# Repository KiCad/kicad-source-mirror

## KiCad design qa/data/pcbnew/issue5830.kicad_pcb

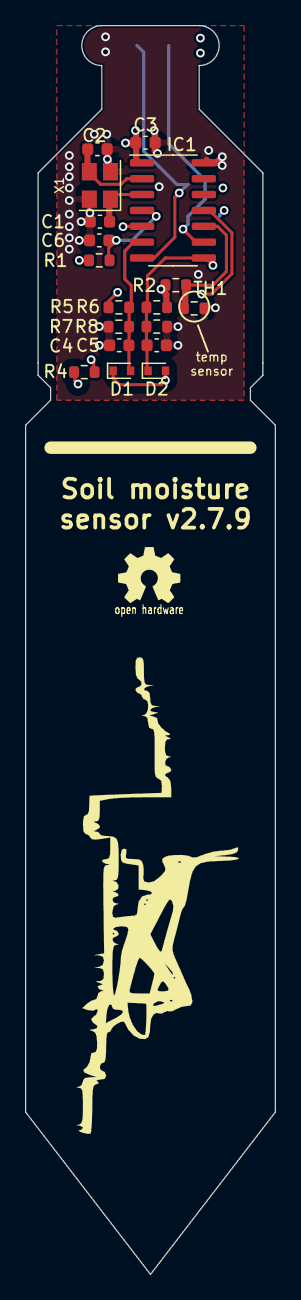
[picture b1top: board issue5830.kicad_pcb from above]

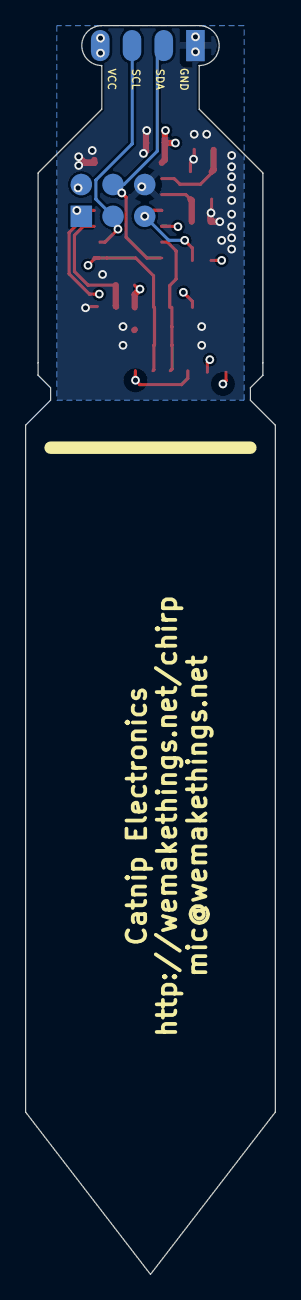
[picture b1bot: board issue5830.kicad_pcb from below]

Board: 4 copper layers, 20.0 x 100.0 mm, 20 parts (2 on the bottom side), 13 nets.

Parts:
C1: 33p; C_0603_1608Metric
C2: 33pp; C_0603_1608Metric
C3, C6: 1u; C_0603_1608Metric
C4, C5: 1n; C_0603_1608Metric
D1, D2: BAT54; D_SOD-523
IC1: ATTINY441-SSU; SOIC-14_3.9x8.7mm_P1.27mm
P1: CONN_02X03; Pin_Header_Straight_2x03
P2: CONN_01X04; Pin_Header_Straight_1x04_Pitch2.54mm
R1: 10k; R_0603_1608Metric
R2: 10k 0.1%; R_0603_1608Metric
R4: 330; R_0603_1608Metric
R5, R6, R7, R8: 1M; R_0603_1608Metric
TH1: NCP18XH103F03RB; R_0603_1608Metric
X1: 16MHz; Crystal_SMD_3225-4pin_3.2x2.5mm

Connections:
/EXCITATION: IC1.5, R4.2
/MISO/SENSE_HIGH: C5.1, D2.2, IC1.8, P1.1, R6.1, R8.2
/MOSI/SDA: IC1.7, P1.4, P2.2
/RESET: C6.1, IC1.4, P1.5, R1.1
/SCK/SCL: IC1.9, P1.3, P2.3
/SENSE_LOW: C4.1, D1.1, IC1.6, R5.1, R7.2
/SENSOR_TRACK: D1.2, D2.1, R4.1
/THERMISTOR: IC1.10, R2.2, TH1.1
GND: C1.2, C2.2, C3.2, C4.2, C5.2, C6.2, IC1.14, P1.6, P2.1, R7.1, R8.1, TH1.2, X1.2, X1.4
unnamed: C1.1, IC1.3, X1.1
unnamed: C2.1, IC1.2, X1.3
unnamed: IC1.11, R2.1, R5.2, R6.2
VCC: C3.1, IC1.1, P1.2, P2.4, R1.2

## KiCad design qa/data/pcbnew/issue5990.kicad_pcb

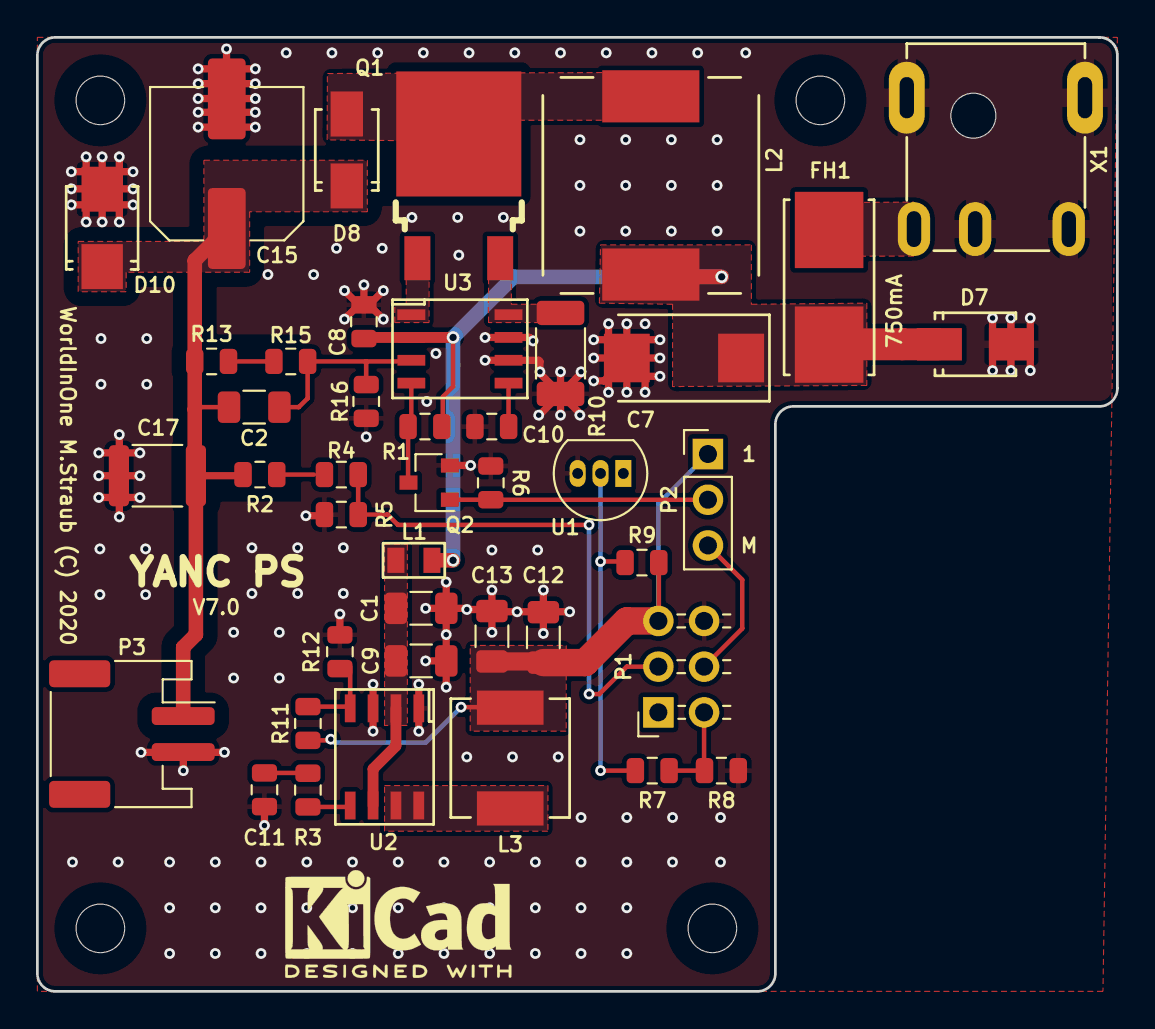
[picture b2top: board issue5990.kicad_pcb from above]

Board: 2 copper layers, 60.0 x 53.0 mm, 46 parts (0 on the bottom side), 23 nets.

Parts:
C1, C9, C12, C13: 22µ; C_1206_3216Metric_95
C2: 100P; C_1206_3216Metric_95
C7: 100µ; Tantalum_Case-D_EIA-7343-31_Reflow
C8, C10: 100N; C_0805_2012Metric_60
C11: 2.7N; C_0805_2012Metric_60
C15: 3.3µ; C_Elec_8x10.2
C17: 100N; C_1812_4532Metric
D7: SS34; SMA_Standard
D8: ES1G; SMA_Standard
D10: SMBJ5388B; SMB_Standard
FH1: FH1808; Littelfuse_Nano2_1808_Fuse_Holder_SMD
L1: FB0805; INDC2012X110
L2: 100µ; CDRH127
L3: 10µ; Inductor_0630
MH1, MH2, MH3, MH4: Mounting_Hole; MountingHole_2.7mm_M2.5_DIN965
P1: FE03-2W; PinSocket_2x03_P2.54mm_Horizontal
P2: MA03-1; PinHeader_1x03_P2.54mm_Vertical
P3: JSTPHMHS-2; JST_PH_S2B-PH-SM4-TB_1x02-1MP_P2.00mm_Horizontal
Q1: FQD18N20; TO-252
Q2: BSS138; SOT-23
R1, R3: 22K; R_0805_2012Metric
R2, R13, R15: 470K; R_0805_2012Metric
R4, R6, R8, R12: 10K; R_0805_2012Metric
R5: 3.9K; R_0805_2012Metric
R7: 15K; R_0805_2012Metric
R9: 1K; R_0805_2012Metric
R10: 0.05E; R_2010_5025Metric
R11: 52.3K; R_0805_2012Metric
R16: 8.2K; R_0805_2012Metric
U1: LM335Z; TO-92_Inline_Narrow_Oval
U2: AOZ1015AI; SOIC-8_3.9x4.9mm_Pitch1.27mm
U3: MAX1771; SOIC-8_3.9x4.9mm_Pitch1.27mm
X1: PJ-051A

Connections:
/5V: C12.2, C13.2, L3.2, P1.5, P2.1, R9.1, R11.2
/170V: C2.1, C15.1, C17.1, D8.1 (K), D10.1 (K), P3.1, R2.2, R13.2
/CASETEMP: P1.2, R7.2, R8.1
/HVON: P1.4, P2.3
/U170V: P1.3, R4.1, R5.2
/UB: C1.2, C9.2, L1.2, U2.2 (VIN), U2.6 (EN)
/UIN: C7.1, C8.1, D7.1 (K), FH1.2, L1.1, L2.1, R1.2, U3.2 (VCC)
GND: C1.1, C7.2, C8.2, C9.1, C10.2, C11.1, C12.1, C13.1, C15.2, C17.2, D7.2 (A), D10.2 (A), P1.6, P3.2, Q2.2 (S), R5.1, R6.1, R8.2, R10.2, R12.1, R16.1, U1.3 (-), U2.1 (PGND), U2.3 (AGND), U3.6 (AGND), U3.7 (GND), X1.2, X1.3, X1.CASE (CASE1)
unnamed: C2.2, R15.1, R16.2, U3.3 (FB)
unnamed: C10.1, U3.5 (REF)
unnamed: C11.2, R3.1
unnamed: D8.2 (A), L2.2, Q1.3 (D)
unnamed: FH1.1, X1.1
unnamed: L3.1, U2.7 (LX), U2.8 (LX)
unnamed: P2.2, Q2.1 (G), R6.2
unnamed: Q1.1 (G), U3.1 (EXT)
unnamed: Q1.2 (S), R10.1, U3.8 (CS)
unnamed: Q2.3 (D), R1.1, U3.4 (SHDN)
unnamed: R2.1, R4.2
unnamed: R3.2, U2.5 (COMP)
unnamed: R7.1, R9.2, U1.2 (+)
unnamed: R11.1, R12.2, U2.4 (FB)
unnamed: R13.1, R15.2

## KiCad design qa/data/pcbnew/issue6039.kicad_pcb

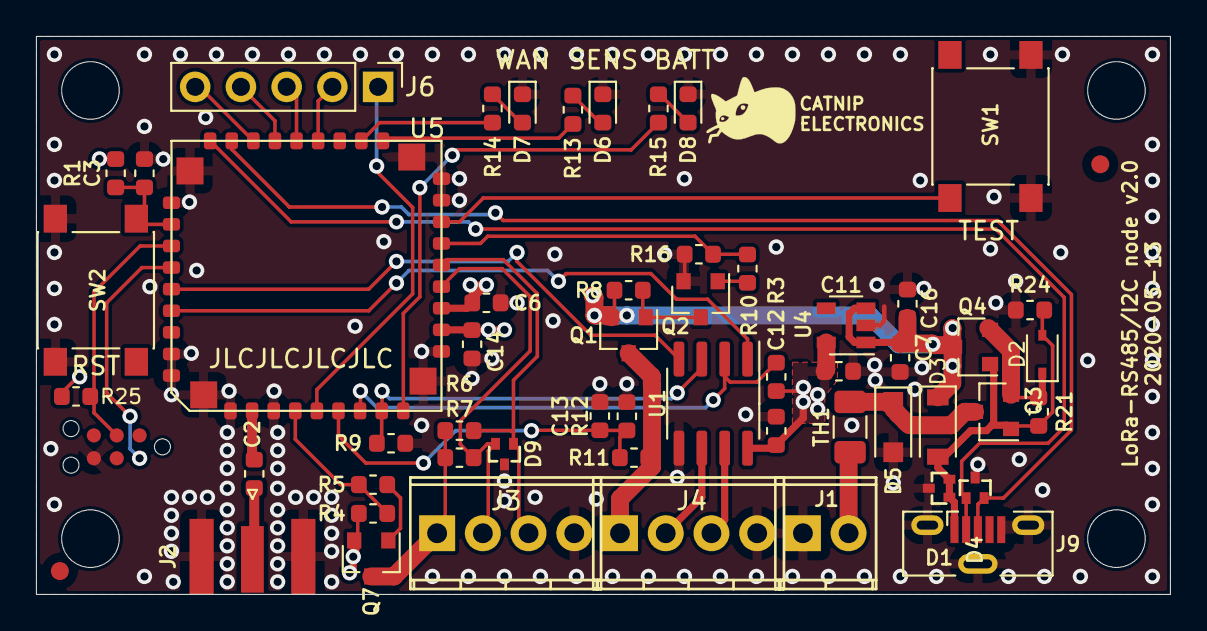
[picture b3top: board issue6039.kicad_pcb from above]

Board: 4 copper layers, 63.0 x 31.0 mm, 60 parts (0 on the bottom side), 42 nets.

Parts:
C2: 47p; C_0603_1608Metric
C3, C6, C12, C13, C14: 1u; C_0603_1608Metric
C7, C11, C16: 4.7u; C_0603_1608Metric
D1, D4, D9: 5V6; SC89
D2: 7.6V; D_SOD-323
D3: 1N4148; D_SOD-123
D5: SMF11A; D_SOD-123F
D6, D7, D8: LED; LED_0603_1608Metric
FID1, FID2: Fiducial; Fiducial_1mm_Dia_2mm_Outer
H1, H2, H3, H4: MountingHole; MountingHole_3.2mm_M3_DIN965
J1: battery; TerminalBlock_Phoenix_MPT-2.54mm_2pol
J2: ANT; SMA_6.35_EdgeMount
J3: i2c; TerminalBlock_Phoenix_MPT-2.54mm_4pol
J4: rs485; TerminalBlock_Phoenix_MPT-2.54mm_4pol
J5: SWD; TC2030-MCP-NL
J6: Conn_01x05_Female; Pin_Header_Straight_1x05_Pitch2.54mm
J9: USB micro; USB_Micro-B_Vertical_Molex-105133-0001
Q1, Q3, Q4, Q7: NX2301P; SOT-23
Q2: NTR4003; SOT-23
R1, R13, R14, R15, R25: 1k; R_0603_1608Metric
R3, R4, R8, R9, R16, R21, R24: 1M; R_0603_1608Metric
R5, R10: 150; R_0603_1608Metric
R6, R7: 4.7k; R_0603_1608Metric
R11: 20k; R_0603_1608Metric
R12: 10k; R_0603_1608Metric
SW1: SW_Test; SW_Push_1P1T_NO_6x6mm_H9.5mm
SW2: SW_Reset; SW_Push_1P1T_NO_6x6mm_H9.5mm
TH1: Thermistor_PTC; Fuse_1206_3216Metric
U1: SN65HVD72; SOIC-8_3.9x4.9mm_P1.27mm
U4: NCP718; SOT-23-5
U5: RAK4260; RAK4260-footprint_w_solder_paste

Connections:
+3V3: C6.1, C11.1, C12.1, C14.1, Q7.2 (S), R1.1, R3.1, R4.2, R25.1, U1.8 (VCC), U4.5 (Vout), U5.11 (VCC3V3), U5.12 (VCC3V3)
+BATT: C7.1, C16.1, D3.1 (K), Q1.2 (S), Q4.3 (D), R8.2, U4.1 (Vin), U4.3 (~SHDN)
/A: J4.2, U1.6 (A)
/A1: J6.1, U5.5 (PA06)
/ANTENNA: C2.2, J2.1
/B: J4.3, U1.7 (B)
/BATT_MON: C13.1, R11.2, R12.2, U5.6 (PA07)
/D+: D4.2 (A2), J9.3 (D+), U5.26 (PA25_USB_P)
/D-: D4.1 (A1), J9.2 (D-), U5.27 (PA24_USB_N)
/I2C_SCL: D9.2 (A2), J3.2, R7.2, U5.13 (PA17_SCL)
/I2C_SDA: D9.1 (A1), J3.3, R6.2, U5.14 (PA16_SDA)
/LED1: R13.1, U5.19 (PA18_UART3_RX)
/LED2: R14.1, U5.20 (PA19_UART3_TX)
/LED3: R15.1, U5.9 (PB22)
/MISO: J6.2, U5.22 (PA23_MOSI)
/MOSI: J6.5, U5.25 (PB02_MISO)
/RF: C2.1, U5.2 (RFC)
/RS485_DE: R9.1, U1.3 (DE), U5.8 (PA09)
/RS485_ENABLE: R10.2, R16.1, U5.15 (PA15)
/RX: U1.1 (RO), U5.33 (PA05_UART1_RX)
/SCK: J6.4, U5.24 (PB23_SCK)
/SS: J6.3, U5.23 (PA22_SS)
/SWD_CLK: J5.3, R25.2, U5.30 (PA30_SWDCLK)
/SWD_IO: J5.2, U5.31 (PA31_SWDIO)
/TX: U1.4 (DI), U5.32 (PA04_UART1_TX)
/VIN: J1.2, TH1.1
/VOUT: J3.1, Q7.3 (D), R6.1, R7.1
/VOUT_1: J4.1, Q1.3 (D), R11.1
/~I2C_ENABLE: R4.1, R5.2, U5.4 (PA27)
/~MCU_RST: C3.1, R1.2, SW2.2, U5.29 (RST)
/~RS485_RE: R3.2, U1.2 (~RE~), U5.7 (PA08)
GND: C3.2, C6.2, C7.2, C11.2, C12.2, C13.2, C14.2, C16.2, D1.3 (common), D4.3 (common), D5.2 (A2), D6.1 (K), D7.1 (K), D8.1 (K), D9.3 (common), J1.1, J2.2, J3.4, J4.4, J5.6, J9.5 (GND), J9.6 (Shield), Q2.2 (S), R9.2, R12.1, R16.2, R24.2, SW1.1, SW2.1, U1.5 (GND), U4.2 (GND), U5.1 (GND), U5.3 (GND), U5.10 (GND), U5.17 (GND), U5.18 (GND), U5.28 (GND), U5.35 (GND), U5.36 (GND), U5.37 (GND)
unnamed: D2.1 (K), Q3.2 (S), Q4.2 (S), R21.1
unnamed: D5.1 (A1), Q3.3 (D), TH1.2
unnamed: D6.2 (A), R13.2
unnamed: D7.2 (A), R14.2
unnamed: D8.2 (A), R15.2
unnamed: Q1.1 (G), Q2.3 (D), R8.1
unnamed: Q2.1 (G), R10.1
unnamed: Q7.1 (G), R5.1
unnamed: SW1.2, U5.16 (PA14)
VBUS: D1.1 (A1), D1.2 (A2), D2.2 (A), D3.2 (A), J9.1 (VBUS), Q3.1 (G), Q4.1 (G), R21.2, R24.1

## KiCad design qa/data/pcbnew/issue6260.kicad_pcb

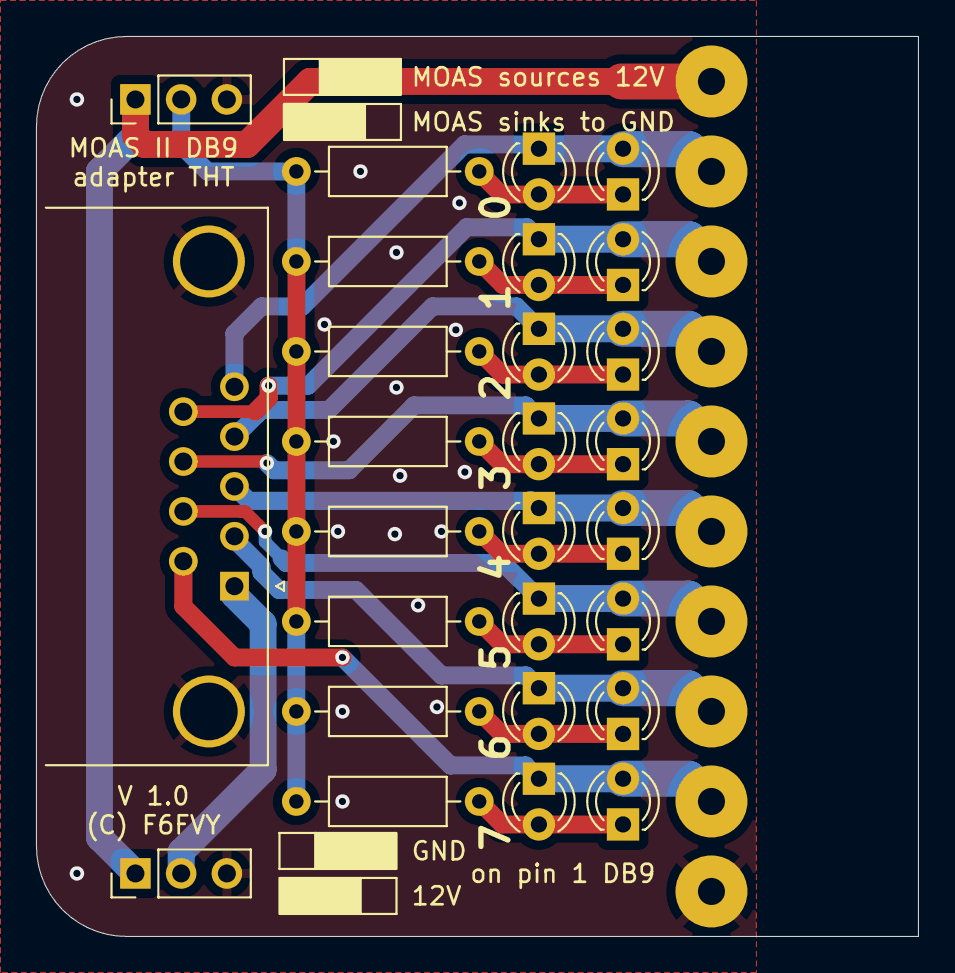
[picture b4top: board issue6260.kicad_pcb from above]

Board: 2 copper layers, 49.0 x 50.0 mm, 37 parts (0 on the bottom side), 20 nets.

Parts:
D1, D2, D3, D4, D5, D6, D7, D8, D9, D10, D11, D12, D13, D14, D15, D16: LED; LED_D3.0mm
J1, J2, J3, J4, J5, J6, J7, J8, J9, J10: Conn_01x01; SolderWirePad_1x01_Drill1.5mm
J11, J12: Conn_01x03; PinHeader_1x03_P2.54mm_Vertical
J13: DB9_Female_MountingHoles; DSUB-9_Female_Horizontal_P2.77x2.84mm_EdgePinOffset7.70mm_H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
R1, R2, R3, R4, R5, R6, R7, R8: 4k7; R_Axial_DIN0207_L6.3mm_D2.5mm_P10.16mm_Horizontal

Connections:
+12V: J1.1, J11.1, J12.1
GND: J10.1, J11.3, J12.3, J13.0 (PAD)
unnamed: D1.1 (K), D9.2 (A), J2.1, J13.5
unnamed: D1.2 (A), D9.1 (K), R1.1
unnamed: D2.2 (A), D10.1 (K), R2.1
unnamed: D2.1 (K), D10.2 (A), J3.1, J13.9
unnamed: D3.2 (A), D11.1 (K), R3.1
unnamed: D3.1 (K), D11.2 (A), J4.1, J13.4
unnamed: D4.2 (A), D12.1 (K), R4.1
unnamed: D4.1 (K), D12.2 (A), J5.1, J13.8
unnamed: D5.2 (A), D13.1 (K), R5.1
unnamed: D5.1 (K), D13.2 (A), J6.1, J13.3
unnamed: D6.2 (A), D14.1 (K), R6.1
unnamed: D6.1 (K), D14.2 (A), J7.1, J13.7
unnamed: D7.2 (A), D15.1 (K), R7.1
unnamed: D7.1 (K), D15.2 (A), J8.1, J13.2
unnamed: D8.2 (A), D16.1 (K), R8.1
unnamed: D8.1 (K), D16.2 (A), J9.1, J13.6
unnamed: J11.2, R1.2, R2.2, R3.2, R4.2, R5.2, R6.2, R7.2, R8.2
unnamed: J12.2, J13.1

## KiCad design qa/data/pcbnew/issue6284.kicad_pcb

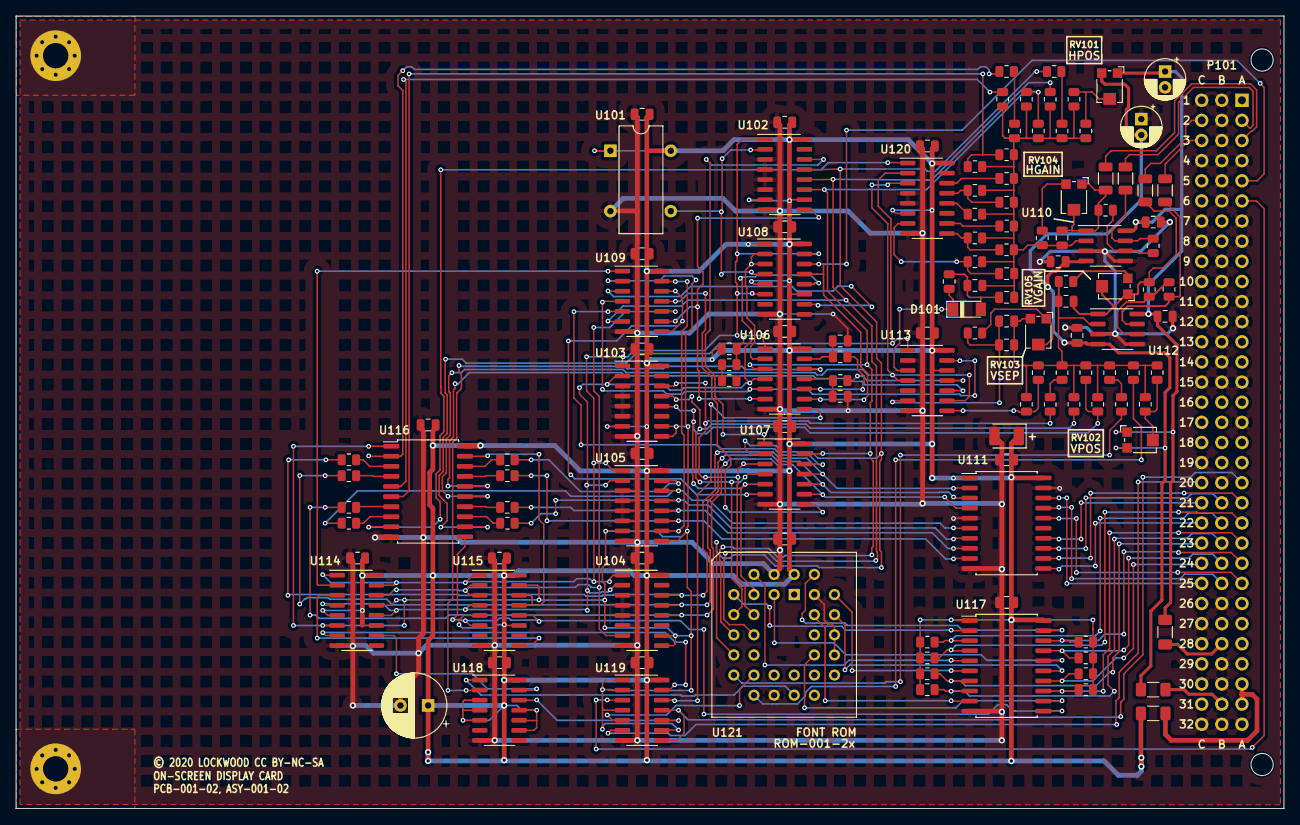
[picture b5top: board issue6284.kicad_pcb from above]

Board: 2 copper layers, 160.0 x 100.0 mm, 134 parts (0 on the bottom side), 127 nets.

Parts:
C101, C104, C105, C106, C108: 100p; C_0805_2012Metric
C102, C103: 47p; C_0805_2012Metric
C107, C109, C110: 330p; C_0805_2012Metric
CD101: 470µ; CP_Radial_D8.0mm_P3.50mm
CD102: 10µ; CP_EIA-3528-21_Kemet-B
CD103, CD104, CD105, CD106, CD107, CD108, CD109, CD110, CD111, CD112, CD113, CD114, CD115, CD116, CD117, CD118, CD119, CD120, CD121, CD123, CD124, CD126, CD127: 1µ; C_0805_2012Metric
CD122, CD125: 47µ; CP_Radial_D5.0mm_P2.00mm
D101: LL4448; D_MiniMELF
H101, H102: HOLE; MountingHole_3.2mm_M3_Pad_Via
P101: DIN41612_M_3x32_OS2; DIN41612_B_3x32_Horizontal
R101, R102, R103, R104, R105, R106, R107, R108, R155, R156: 2k37; R_0805_2012Metric
R109, R110, R112, R113, R114, R115, R116, R117, R118, R119, R128, R133, R137, R142, R143, R147, R148, R149, R150, R151: 39k; R_0805_2012Metric
R111, R120, R123, R125, R126: 1k96; R_0805_2012Metric
R121, R136: 680k; R_0805_2012Metric
R122, R129, R130, R131, R138, R152, R153, R154: 205k; R_0805_2012Metric
R124, R134, R135, R157, R158, R159, R160: 5k9; R_0805_2012Metric
R127, R132, R144, R145, R146: 274k; R_0805_2012Metric
R139, R140, R141: 9k76; R_0805_2012Metric
R161, R162, R163, R164: 1k5; R_1206_3216Metric
RT101, RT102, RT103: 250mA; R_1206_3216Metric_Pad1.30x1.75mm_HandSolder
RV101, RV102: 20k; Potentiometer_Bourns_TC33X_Vertical
RV103: 1k; Potentiometer_Bourns_TC33X_Vertical
RV104, RV105: 500; Potentiometer_Bourns_TC33X_Vertical
U101: 2MHz; Oscillator_SeikoEpson_SG-8002DC
U102, U103, U104, U105: 'HC161; SOIC-16_3.9x9.9mm_P1.27mm
U106: 'HC14; SOIC-14_3.9x8.7mm_P1.27mm
U107, U118: 'HC10; SOIC-14_3.9x8.7mm_P1.27mm
U108, U114, U115: 'HC109; SOIC-16_3.9x9.9mm_P1.27mm
U109: 'HC02; SOIC-14_3.9x8.7mm_P1.27mm
U110, U112: NE5532; SOIC-8_3.9x4.9mm_P1.27mm
U111: 'HC245; SOIC-20W_7.5x12.8mm_P1.27mm
U113: 'HC86; SOIC-14_3.9x8.7mm_P1.27mm
U116, U117: 'HCT273; SOIC-20W_7.5x12.8mm_P1.27mm
U119: 'HC03; SOIC-14_3.9x8.7mm_P1.27mm
U120: 'HC237; SOIC-16_3.9x9.9mm_P1.27mm
U121: 27C512; PLCC-32_THT-Socket

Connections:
+15V: CD122.1, CD123.1, CD124.1, RT101.2, RV101.1, RV102.1, U110.8 (V+), U112.8 (V+)
-15V: CD125.2, CD126.1, CD127.1, RT103.2, RV101.3, RV102.3, U110.4 (V-), U112.4 (V-)
/CHAR0: P101.B22 (CHAR0), R108.2, U117.3 (D0)
/CHAR1: P101.A22 (CHAR1), R107.2, U117.4 (D1)
/CHAR2: P101.C23 (CHAR2), R106.2, U117.7 (D2)
/CHAR3: P101.B23 (CHAR3), R105.2, U117.8 (D3)
/CHAR4: P101.A23 (CHAR4), R104.2, U117.13 (D4)
/CHAR5: P101.C24 (CHAR5), R103.2, U117.14 (D5)
/CHAR6: P101.B24 (CHAR6), R102.2, U117.17 (D6)
/CHAR7: P101.A24 (CHINT), R101.2, U117.18 (D7)
/Circuit/CHAR0: U117.2 (Q0), U121.5 (A6)
/Circuit/CHAR1: U117.5 (Q1), U121.4 (A7)
/Circuit/CHAR2: U117.6 (Q2), U121.29 (A8)
/Circuit/CHAR3: U117.9 (Q3), U121.28 (A9)
/Circuit/CHAR4: U117.12 (Q4), U121.24 (A10)
/Circuit/CHAR5: U117.15 (Q5), U121.27 (A11)
/Circuit/CHAR6: U117.16 (Q6), U121.3 (A12)
/Circuit/CHAR7: U117.19 (Q7), U121.30 (A13)
/Circuit/DESCENDER0: R129.2, U121.13 (O0)
/Circuit/DESCENDER1: R138.2, U121.14 (O1)
/Circuit/FINISH#: U114.3 (~K), U115.9 (~Q)
/Circuit/FINISHREQ: R119.2, U105.15 (Tc)
/Circuit/FLD0: U116.9 (Q3), U120.1 (A0)
/Circuit/FLD1: U113.1, U116.12 (Q4), U120.2 (A1)
/Circuit/FLD2: U113.4, U113.9, U116.15 (Q5), U120.3 (A2)
/Circuit/FLD3: U113.10, U116.16 (Q6)
/Circuit/FLDREQ0: R115.2, U105.14 (Q0), U111.6 (A4)
/Circuit/FLDREQ1: R116.2, U105.13 (Q1), U111.7 (A5)
/Circuit/FLDREQ2: R117.2, U105.12 (Q2), U111.8 (A6)
/Circuit/FLDREQ3: R118.2, U105.11 (Q3), U111.9 (A7)
/Circuit/FLD_BOTTOM: R136.1, R137.2, U113.8
/Circuit/HDOT0: R127.2, U102.13 (Q1), U107.2, U121.11 (A0)
/Circuit/HDOT1: R132.2, U102.12 (Q2), U109.6, U121.10 (A1)
/Circuit/HDOT2: R145.2, R146.2, U102.11 (Q3), U106.3, U107.13, U121.9 (A2)
/Circuit/INTEN: U119.5, U121.15 (O2)
/Circuit/INTERLINE_BLANK#: U106.12, U118.2
/Circuit/LASTDOT: U106.5, U109.4, U113.13
/Circuit/LATCHBUS: U115.6 (Q), U115.12 (C), U116.11 (Cp), U117.11 (Cp)
/Circuit/LINE0: R122.2, U103.14 (Q0), U107.3, U121.8 (A3)
/Circuit/LINE1: R153.2, U103.13 (Q1), U107.4, U121.7 (A4)
/Circuit/LINE2: R130.2, R131.2, U103.12 (Q2), U107.5, U121.6 (A5)
/Circuit/NEXTFLDREQ: U105.10 (ENT), U109.13
/Circuit/NEXTPOSREQ: U104.7 (ENP), U109.10, U114.14 (J), U115.2 (J), U115.3 (~K)
/Circuit/PIX_BLANK#: U118.1, U121.18 (O3)
/Circuit/POS0: R128.2, U116.2 (Q0)
/Circuit/POS1: R133.2, U116.5 (Q1)
/Circuit/POS2: R148.2, R149.2, U116.6 (Q2)
/Circuit/POSREQ0: R112.2, U104.14 (Q0), U107.11, U111.2 (A0)
/Circuit/POSREQ1: R113.2, U104.13 (Q1), U107.10, U111.3 (A1)
/Circuit/POSREQ2: R114.2, U104.12 (Q2), U107.9, U111.4 (A2)
/Circuit/READY: U114.10 (Q), U118.13
/Circuit/STARTCMD: U106.8, U119.12
/Circuit/~LASTDOT: U102.9 (~Pe), U106.6, U109.9
/Circuit/~LASTLINE: U107.6, U109.8, U109.12
/Circuit/~LASTPOSREQ: U107.8, U109.11
/FLD0: P101.C21 (SA12), U111.14 (B4)
/FLD1: P101.B21 (SA13), U111.13 (B5)
/FLD2: P101.A21 (SA14), U111.12 (B6)
/FLD3: P101.C22 (SA15), U111.11 (B7)
/H+: P101.A2 (TS+), R162.2
/H-: P101.A3 (TS-), R161.2
/INTEN#: P101.C20 (SA10), U119.6
/POS0: P101.C25 (POS0), U111.18 (B0)
/POS1: P101.B25 (POS1), U111.17 (B1)
/POS2: P101.A25 (POS2), U111.16 (B2)
/RUN#: P101.A6 (SS1), U119.3
/START#: P101.A5 (SS0), U106.9, U108.13 (~K), U108.14 (J)
/V+: P101.C2 (SIG+), R163.2
/V-: P101.C3 (SIG-), R164.2
/ZSEL: P101.A20 (SA11), U119.8, U119.11
DONE: U114.7 (~Q), U119.13
DOTCLK: U101.5 (OUT), U102.2 (CK), U108.4 (C)
GND: C102.2, C103.2, CD101.2, CD102.2, CD103.2, CD104.2, CD105.2, CD106.2, CD107.2, CD108.2, CD109.2, CD110.2, CD111.2, CD112.2, CD113.2, CD114.2, CD115.2, CD116.2, CD117.2, CD118.2, CD119.2, CD120.2, CD121.2, CD122.2, CD123.2, CD124.2, CD125.1, CD126.2, CD127.2, H101.1, H102.1, P101.A1 (GND), P101.A4 (GND), P101.A7 (GND), P101.A8 (GND), P101.A11 (GND), P101.A12 (GND), P101.A15 (GND), P101.A17 (GND), P101.A32 (GND), P101.B1 (GND), P101.B2 (GND), P101.B3 (GND), P101.B4 (GND), P101.B5 (GND), P101.B6 (GND), P101.B9 (GND), P101.B10 (GND), P101.B13 (GND), P101.B14 (GND), P101.B15 (GND), P101.B20 (GND), P101.B26 (GND), P101.B29 (GND), P101.B30 (GND), P101.B32 (GND), P101.C1 (GND), P101.C4 (GND), P101.C7 (GND), P101.C8 (GND), P101.C11 (GND), P101.C12 (GND), P101.C15 (GND), P101.C19 (GND), P101.C27 (GND), P101.C28 (GND), P101.C30 (GND), P101.C32 (GND), R110.2, U101.4 (GND), U102.3 (P0), U102.4 (P1), U102.5 (P2), U102.6 (P3), U102.8 (GND), U103.3 (P0), U103.4 (P1), U103.5 (P2), U103.6 (P3), U103.8 (GND), U104.3 (P0), U104.4 (P1), U104.5 (P2), U104.6 (P3), U104.8 (GND), U105.3 (P0), U105.4 (P1), U105.5 (P2), U105.6 (P3), U105.8 (GND), U106.7 (GND), U107.7 (GND), U108.8 (GND), U109.7 (GND), U110.3 (+), U110.5 (+), U111.5 (A3), U111.10 (GND), U111.19 (CE), U112.3 (+), U112.5 (+), U113.2, U113.5, U113.7 (GND), U114.8 (GND), U115.8 (GND), U116.10 (GND), U117.10 (GND), U118.7 (GND), U119.7 (GND), U120.4 (~LE), U120.5 (~E1), U120.8 (GND), U121.2 (A15), U121.16 (GND), U121.23 (~CE), U121.25 (~OE~/VPP), U121.31 (A14)
unnamed: C101.2, R109.1, U106.1
unnamed: C102.1, R111.1, U106.11
unnamed: C103.1, R120.1, U106.13
unnamed: C104.1, R126.2, U120.7 (Y7)
unnamed: C104.2, C107.2, C108.2, C109.1, R124.1, R125.1, R126.1, R132.1, R133.1, R134.1, R135.1, R139.1, R140.1, R141.1, R142.1, R143.1, R144.1, R145.1, R146.1, R147.1, R148.1, R149.1, R155.1, U110.2 (-)
unnamed: C105.1, C106.1, R123.2, U113.6
unnamed: C105.2, C106.2, C110.1, R130.1, R131.1, R136.2, R137.1, R138.1, R150.1, R151.1, R152.1, R153.1, R154.1, R156.1, RV103.3, U112.2 (-)
unnamed: C107.1, C108.1, D101.2 (A), R121.2
unnamed: C109.2, R157.1, R161.1, RV104.1, RV104.2, U110.1
unnamed: C110.2, R159.1, R163.1, RV105.1, RV105.2, U112.1
unnamed: D101.1 (K), R121.1, U113.3
unnamed: P101.A30 (+5V), P101.A31 (+5V), RT102.1
unnamed: P101.B28 (+15V), RT101.1
unnamed: P101.B31 (-15V), RT103.1
unnamed: R109.2, R110.1
unnamed: R111.2, U113.11
unnamed: R112.1, U116.3 (D0)
unnamed: R113.1, U116.4 (D1)
unnamed: R114.1, U116.7 (D2)
unnamed: R115.1, U116.8 (D3)
unnamed: R116.1, U116.13 (D4)
unnamed: R117.1, U116.14 (D5)
unnamed: R118.1, U116.17 (D6)
unnamed: R119.1, U116.18 (D7)
unnamed: R120.2, U106.10
unnamed: R122.1, R152.2
unnamed: R123.1, RV103.1, RV103.2
unnamed: R124.2, U120.14 (Y1)
unnamed: R125.2, U120.12 (Y3)
unnamed: R127.1, R144.2
unnamed: R128.1, R147.2
unnamed: R129.1, R154.2
unnamed: R134.2, R135.2, U120.13 (Y2)
unnamed: R139.2, U120.10 (Y5)
unnamed: R140.2, R141.2, U120.9 (Y6)
unnamed: R142.2, R143.2, RV101.2
unnamed: R150.2, R151.2, RV102.2
unnamed: R155.2, RV104.3
unnamed: R156.2, RV105.3
unnamed: R157.2, R158.2, U110.6 (-)
unnamed: R158.1, R162.1, U110.7
unnamed: R159.2, R160.2, U112.6 (-)
unnamed: R160.1, R164.1, U112.7
unnamed: U102.14 (Q0), U107.1
unnamed: U106.2, U108.2 (J), U108.3 (~K)
unnamed: U107.12, U109.5
unnamed: U108.10 (Q), U109.3
unnamed: U109.1, U114.2 (J)
unnamed: U115.13 (~K), U115.14 (J), U116.19 (Q7)
unnamed: U118.12, U119.10
POR#: U102.1 (~MR), U103.1 (~MR), U104.1 (~MR), U105.1 (~MR), U108.6 (Q), U108.15 (~R), U114.1 (~R), U114.15 (~R), U115.1 (~R)
REQCLK: U103.2 (CK), U104.2 (CK), U105.2 (CK), U106.4, U108.12 (C), U114.4 (C), U114.12 (C), U115.4 (C)
RUN: U103.9 (~Pe), U103.10 (ENT), U104.9 (~Pe), U104.10 (ENT), U105.7 (ENP), U105.9 (~Pe), U109.2, U114.6 (Q), U114.13 (~K), U115.15 (~R), U116.1 (~Mr), U119.1, U119.2, U119.4, U119.9
VCC: C101.1, CD101.1, CD102.1, CD103.1, CD104.1, CD105.1, CD106.1, CD107.1, CD108.1, CD109.1, CD110.1, CD111.1, CD112.1, CD113.1, CD114.1, CD115.1, CD116.1, CD117.1, CD118.1, CD119.1, CD120.1, CD121.1, R101.1, R102.1, R103.1, R104.1, R105.1, R106.1, R107.1, R108.1, RT102.2, U101.1 (OE), U101.8 (Vcc), U102.7 (ENP), U102.10 (ENT), U102.16 (VCC), U103.7 (ENP), U103.16 (VCC), U104.16 (VCC), U105.16 (VCC), U106.14 (VCC), U107.14 (VCC), U108.1 (~R), U108.5 (~S), U108.11 (~S), U108.16 (VCC), U109.14 (VCC), U111.1 (A->B), U111.20 (VCC), U113.12, U113.14 (VCC), U114.5 (~S), U114.11 (~S), U114.16 (VCC), U115.5 (~S), U115.11 (~S), U115.16 (VCC), U116.20 (VCC), U117.1 (~Mr), U117.20 (VCC), U118.3, U118.4, U118.5, U118.9, U118.10, U118.11, U118.14 (VCC), U119.14 (VCC), U120.6 (E2), U120.16 (VCC), U121.32 (VCC)

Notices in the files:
qa/data/pcbnew/issue5990.kicad_pcb:
WorldInOne M.Straub (C) 2020
qa/data/pcbnew/issue6284.kicad_pcb:
© 2020 LOCKWOOD CC BY-NC-SA
